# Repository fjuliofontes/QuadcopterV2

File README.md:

# Quadcopter V2
## This repository contains a work in progress of the second version of my previous quadcopter project.
## This version will support all modes of control.

### Main controller board hardware:
  - 1 x [ESP-01 for Wifi support](https://www.aliexpress.com/item/33018645469.html)
  - 1 x [HC-SR04 for landing support](https://www.aliexpress.com/item/32981718332.html)
  - 1 x [HC-05 for Bluetooth support](https://www.aliexpress.com/item/32953559442.html)
  - 2 x [HC-12 for RF communication](https://www.aliexpress.com/item/32971735328.html)
  - 1 x [MPU-6050 gyro/accelerometer for auto-level feature](https://www.aliexpress.com/item/32346328217.html)
  - 1 x [MS5611 Barometer for altitude hold function](https://www.aliexpress.com/item/4000436844936.html)
  - 1 x [SIM800L V2 for GSM & TCP communication](https://www.aliexpress.com/item/32467842817.html)
  - 1 x [U-blox M8 Engine GPS for heading lock and GPS hold function](https://www.dx.com/p/72-channel-u-blox-m8-engine-gps-module-for-fpv-multicopter-black-2069966.html)
  - 1 x [Texas-EK-TM4C123GXL for running the main software](http://www.ti.com/tool/EK-TM4C123GXL)
  
 ### Quadcopter housing hardware:
  - 1 x [450 size frame with integrated power distribution board](https://www.aliexpress.com/item/4000129400366.html)
  - 4 x [1000kV motor / 10x4.5 props / ESC combo](https://www.aliexpress.com/item/2035093137.html)
  - 1 x [3S / 2200mAh / 30C lipo](https://www.dx.com/p/11-1v-2200mah-30c-li-polymer-battery-pack-for-450-helicopter-dji-phantom-1-450-quadcopter-2048977.html#.Xlpl7C2tEWo)
  - 1 x [Battery XT60 connector](https://www.aliexpress.com/item/33061763696.html)
  - 1 x [2S/3S lipo battery charger](https://www.aliexpress.com/item/4000106254839.html)
  
  #### [Version 1.0](https://github.com/fjuliofontes/Quadcopter)
  
  ##### TODO:
  - [x] Order the necessary hardware.
  - [x] Test and develop code for ordered hardware.
  - [x] Design a schematic and a board for the hardware.
  - [x] Develop a controller algorithm for the quadcopter.
  - [x] Update the android remote controller application.
  - [x] Testing all together. 
  
  ##### Media:

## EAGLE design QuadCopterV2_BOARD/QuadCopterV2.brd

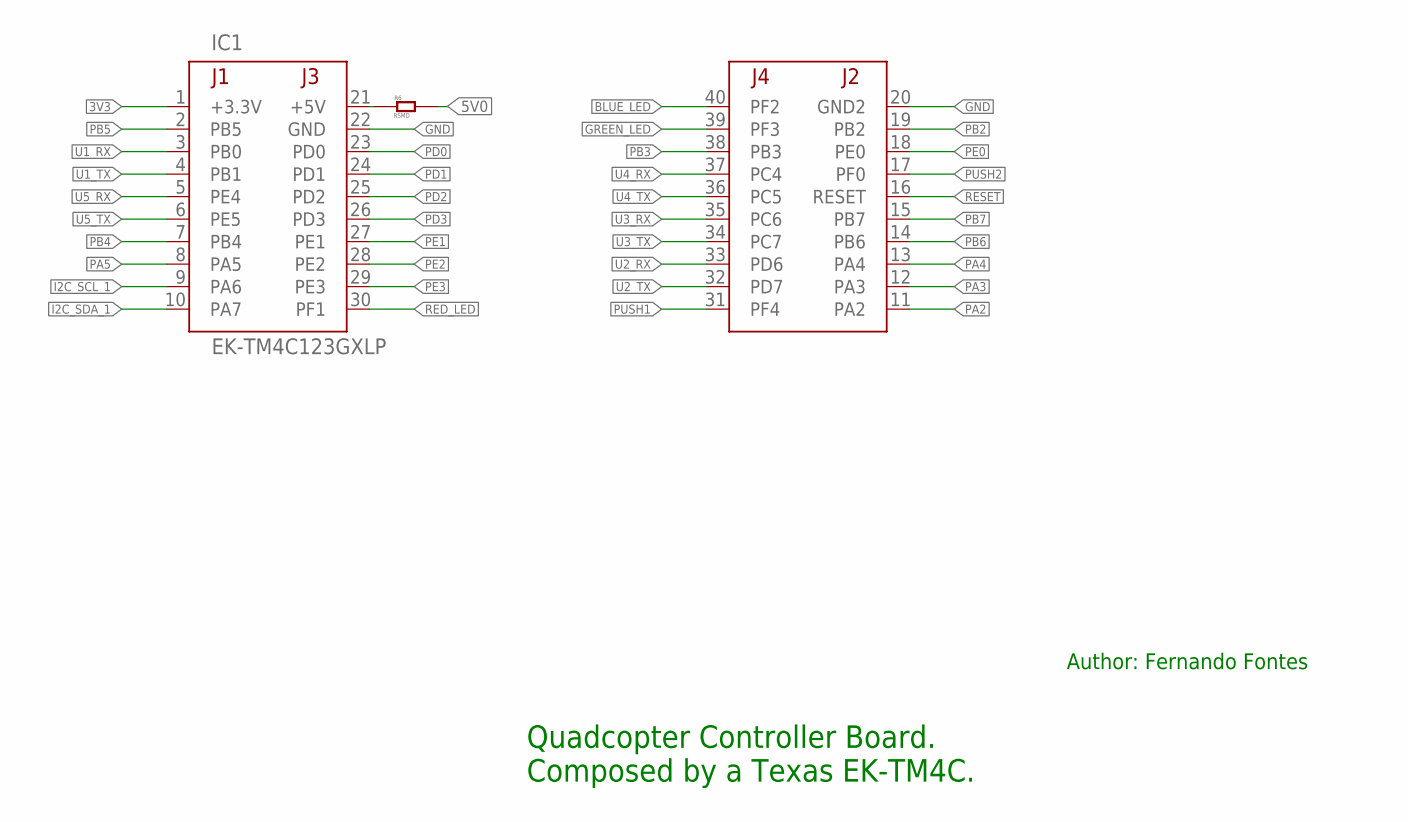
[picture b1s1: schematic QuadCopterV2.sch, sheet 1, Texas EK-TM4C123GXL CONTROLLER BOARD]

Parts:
IC1: EK-TM4C123GXLP; TM4C123LAUNCHPAD
R6: RSMD

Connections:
3V3: IC1.1 (+3.3V)
5V0: R6.2; also elsewhere on the board
BLUE_LED: IC1.40 (PF2)
GND: IC1.20 (GND2), IC1.22 (GND); also elsewhere on the board
GREEN_LED: IC1.39 (PF3)
I2C_SCL_1: IC1.9 (PA6); also elsewhere on the board
I2C_SDA_1: IC1.10 (PA7); also elsewhere on the board
unnamed: IC1.21 (+5V), R6.1
PA2: IC1.11 (PA2); also elsewhere on the board
PA3: IC1.12 (PA3)
PA4: IC1.13 (PA4)
PA5: IC1.8 (PA5); also elsewhere on the board
PB2: IC1.19 (PB2); also elsewhere on the board
PB3: IC1.38 (PB3)
PB4: IC1.7 (PB4); also elsewhere on the board
PB5: IC1.2 (PB5); also elsewhere on the board
PB6: IC1.14 (PB6); also elsewhere on the board
PB7: IC1.15 (PB7); also elsewhere on the board
PD0: IC1.23 (PD0); also elsewhere on the board
PD1: IC1.24 (PD1); also elsewhere on the board
PD2: IC1.25 (PD2)
PD3: IC1.26 (PD3); also elsewhere on the board
PE0: IC1.18 (PE0)
PE1: IC1.27 (PE1); also elsewhere on the board
PE2: IC1.28 (PE2); also elsewhere on the board
PE3: IC1.29 (PE3)
PUSH1: IC1.31 (PF4)
PUSH2: IC1.17 (PF0)
RED_LED: IC1.30 (PF1)
RESET: IC1.16 (RESET)
U1_RX: IC1.3 (PB0); also elsewhere on the board
U1_TX: IC1.4 (PB1); also elsewhere on the board
U2_RX: IC1.33 (PD6); also elsewhere on the board
U2_TX: IC1.32 (PD7); also elsewhere on the board
U3_RX: IC1.35 (PC6); also elsewhere on the board
U3_TX: IC1.34 (PC7); also elsewhere on the board
U4_RX: IC1.37 (PC4); also elsewhere on the board
U4_TX: IC1.36 (PC5); also elsewhere on the board
U5_RX: IC1.5 (PE4); also elsewhere on the board
U5_TX: IC1.6 (PE5); also elsewhere on the board

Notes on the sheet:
Quadcopter Controller Board. Composed by a Texas EK-TM4C.
Author: Fernando Fontes

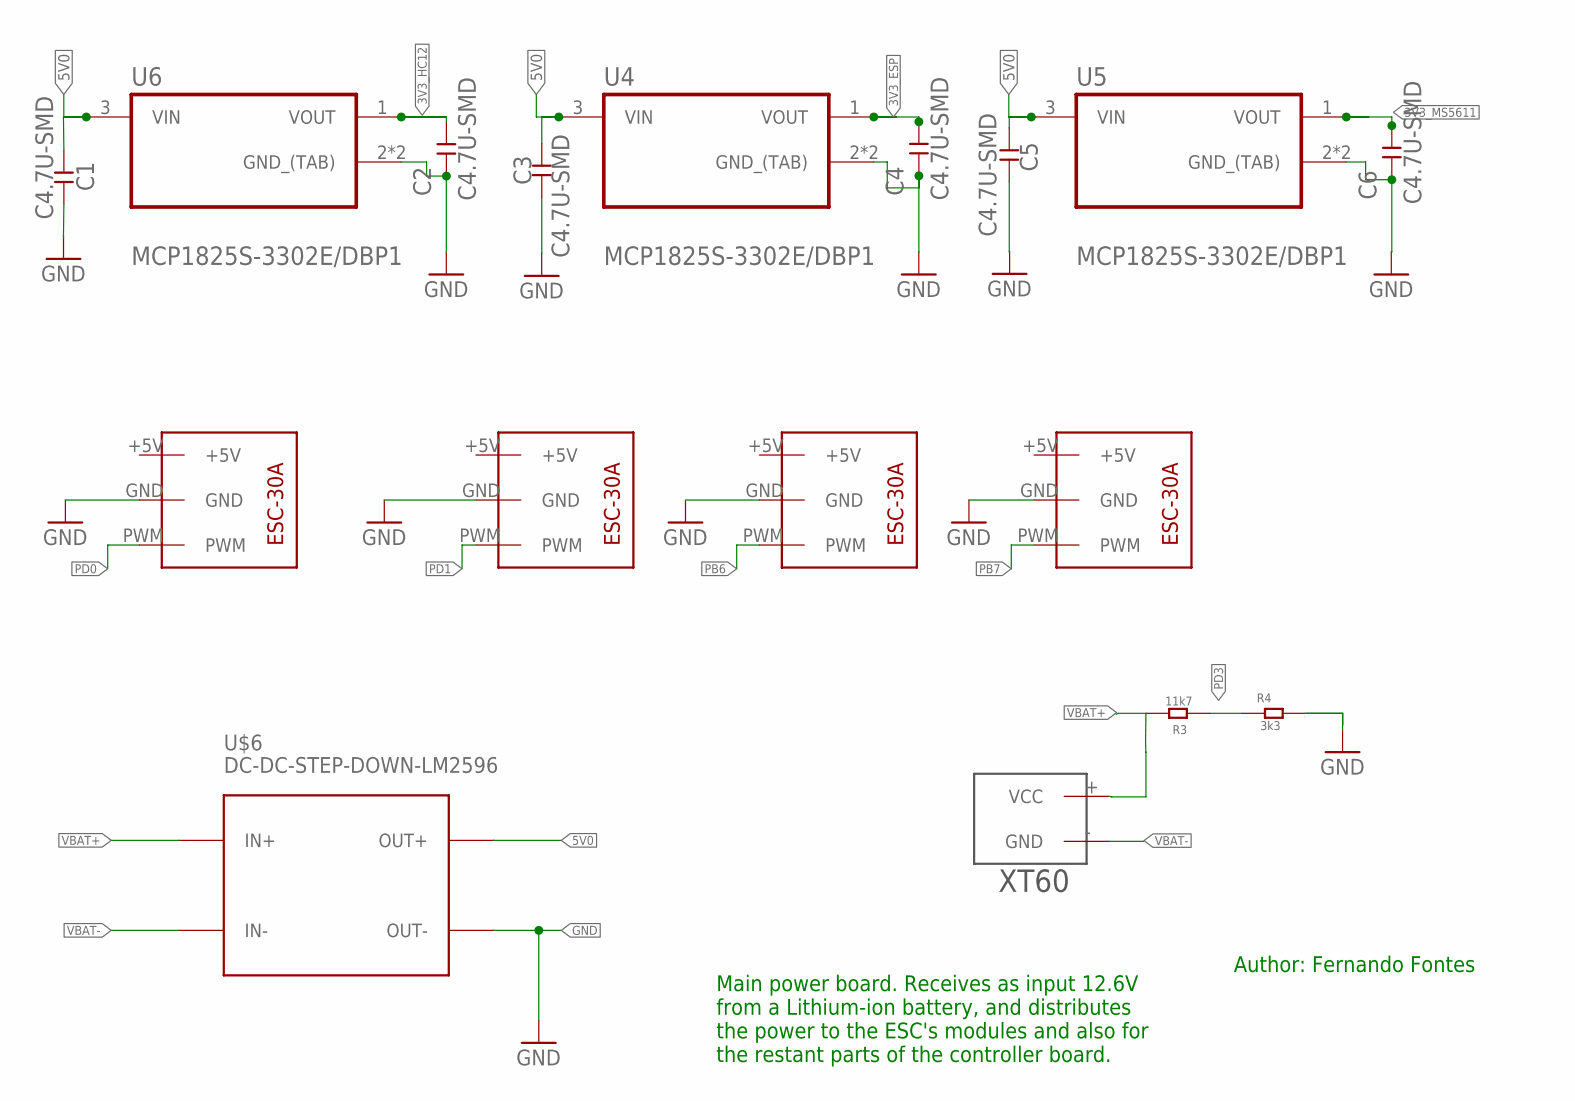
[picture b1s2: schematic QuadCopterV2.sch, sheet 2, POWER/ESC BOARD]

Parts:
C1, C2, C3, C4, C5, C6: C4.7U-SMD
R3: 11k7; RSMD
R4: 3k3; RSMD
U4, U5, U6: MCP1825S-3302E/DBP1; SOT230P700X180-4N#P1
U7, U8, U9, U10: ESC-30AMS5611; ESC-30A
U$6: DC-DC-STEP-DOWN-LM2596
U$7: XT60

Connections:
3V3_ESP: C4.2, U4.1 (VOUT); also elsewhere on the board
3V3_HC12: C2.2, U6.1 (VOUT); also elsewhere on the board
3V3_MS5611: C6.2, U5.1 (VOUT); also elsewhere on the board
5V0: C1.1, C3.2, C5.1, U4.3 (VIN), U5.3 (VIN), U6.3 (VIN), U$6.OUT+; also elsewhere on the board
GND: C1.2, C2.1, C3.1, C4.1, C5.2, C6.1, R4.2, U4.2 (GND_(TAB)), U4.4 (GND_(TAB)), U5.2 (GND_(TAB)), U5.4 (GND_(TAB)), U6.2 (GND_(TAB)), U6.4 (GND_(TAB)), U7.GND, U8.GND, U9.GND, U10.GND, U$6.OUT-; also elsewhere on the board
PB6: U9.PWM; also elsewhere on the board
PB7: U10.PWM; also elsewhere on the board
PD0: U7.PWM; also elsewhere on the board
PD1: U8.PWM; also elsewhere on the board
PD3: R3.1, R4.1; also elsewhere on the board
VBAT+: R3.2, U$6.IN+, U$7.+ (VCC)
VBAT-: U$6.IN-, U$7.- (GND)

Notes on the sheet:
Main power board. Receives as input 12.6V from a Lithium-ion battery, and distributes the power to the ESC's modules and also for the restant parts of the controller board.
Author: Fernando Fontes

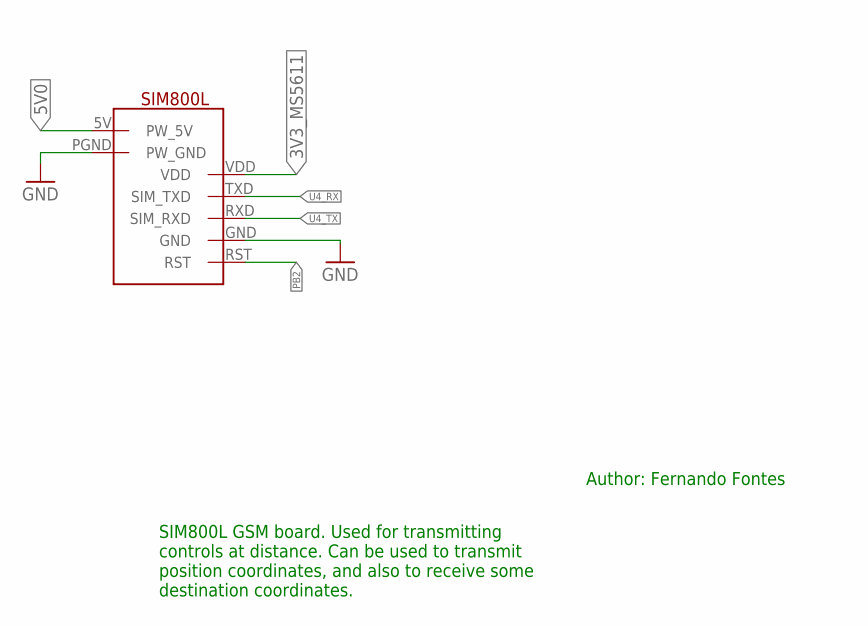
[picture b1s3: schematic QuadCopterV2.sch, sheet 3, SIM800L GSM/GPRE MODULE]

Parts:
U$1: SIM800L; SIP

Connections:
3V3_MS5611: U$1.VDD; also elsewhere on the board
5V0: U$1.5V (PW_5V); also elsewhere on the board
GND: U$1.GND, U$1.PGND (PW_GND); also elsewhere on the board
PB2: U$1.RST; also elsewhere on the board
U4_RX: U$1.TXD (SIM_TXD); also elsewhere on the board
U4_TX: U$1.RXD (SIM_RXD); also elsewhere on the board

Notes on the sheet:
Author: Fernando Fontes
SIM800L GSM board. Used for transmitting controls at distance. Can be used to transmit position coordinates, and also to receive some destination coordinates.

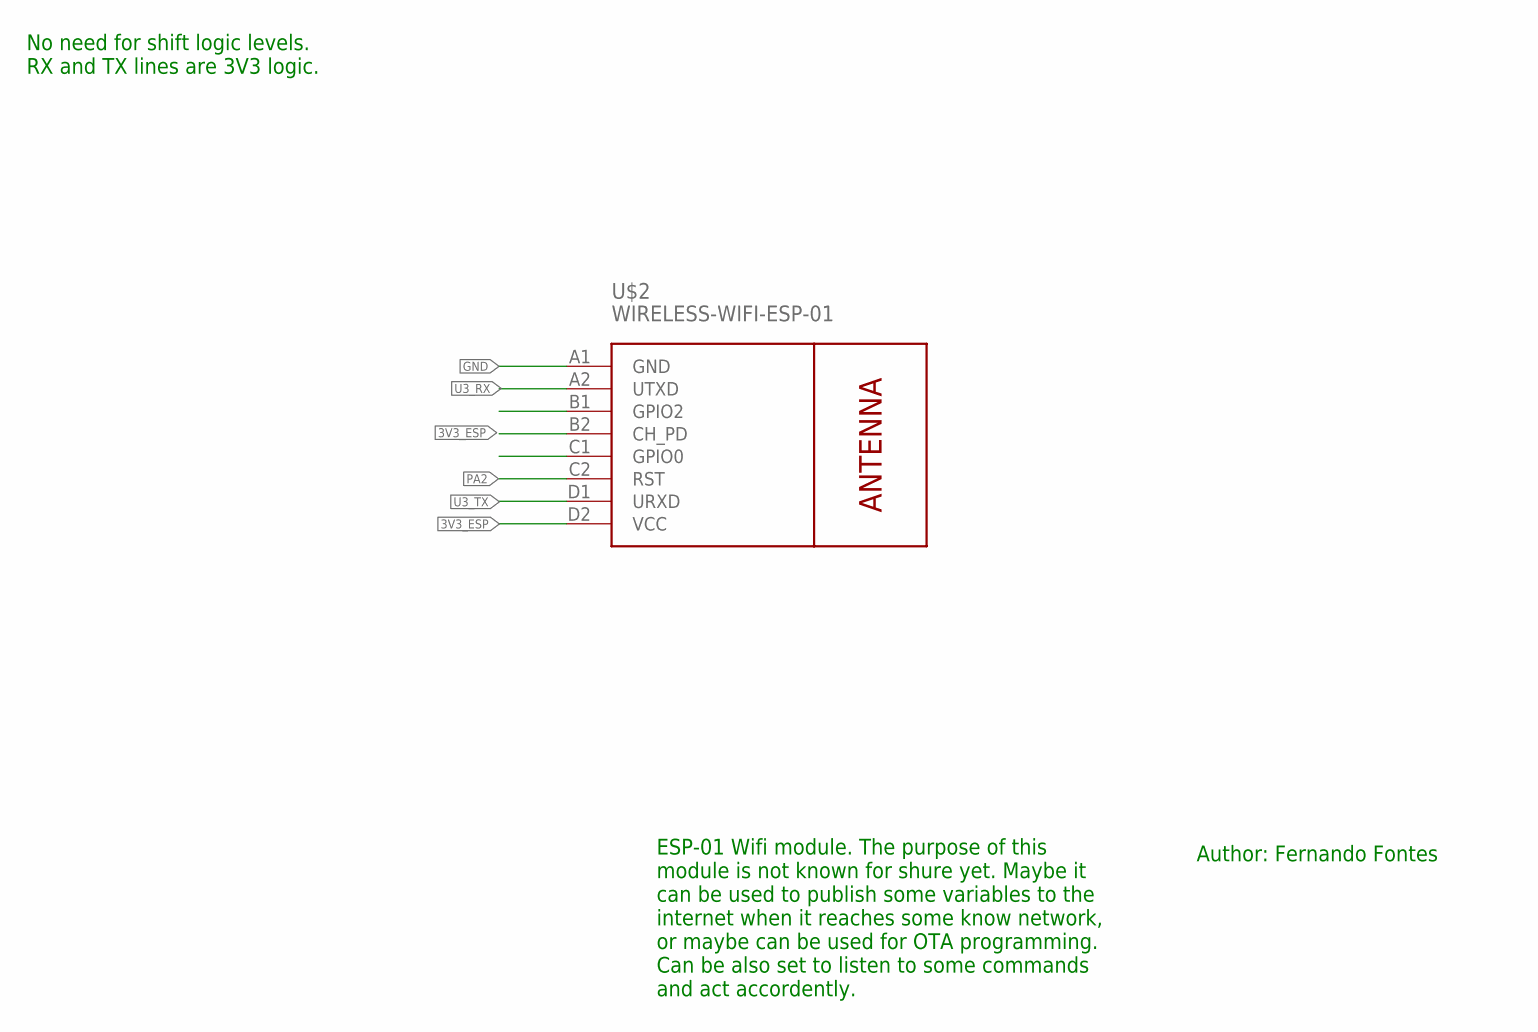
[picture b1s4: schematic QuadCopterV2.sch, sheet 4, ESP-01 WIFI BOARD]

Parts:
U$2: WIRELESS-WIFI-ESP-01

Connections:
3V3_ESP: U$2.B2 (CH_PD), U$2.D2 (VCC); also elsewhere on the board
GND: U$2.A1 (GND); also elsewhere on the board
PA2: U$2.C2 (RST); also elsewhere on the board
U3_RX: U$2.A2 (UTXD); also elsewhere on the board
U3_TX: U$2.D1 (URXD); also elsewhere on the board

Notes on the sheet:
No need for shift logic levels. RX and TX lines are 3V3 logic.
Author: Fernando Fontes
ESP-01 Wifi module. The purpose of this module is not known for shure yet. Maybe it can be used to publish some variables to the internet when it reaches some know network, or maybe can be used for OTA programming. Can be also set to listen to some commands and act accordently.

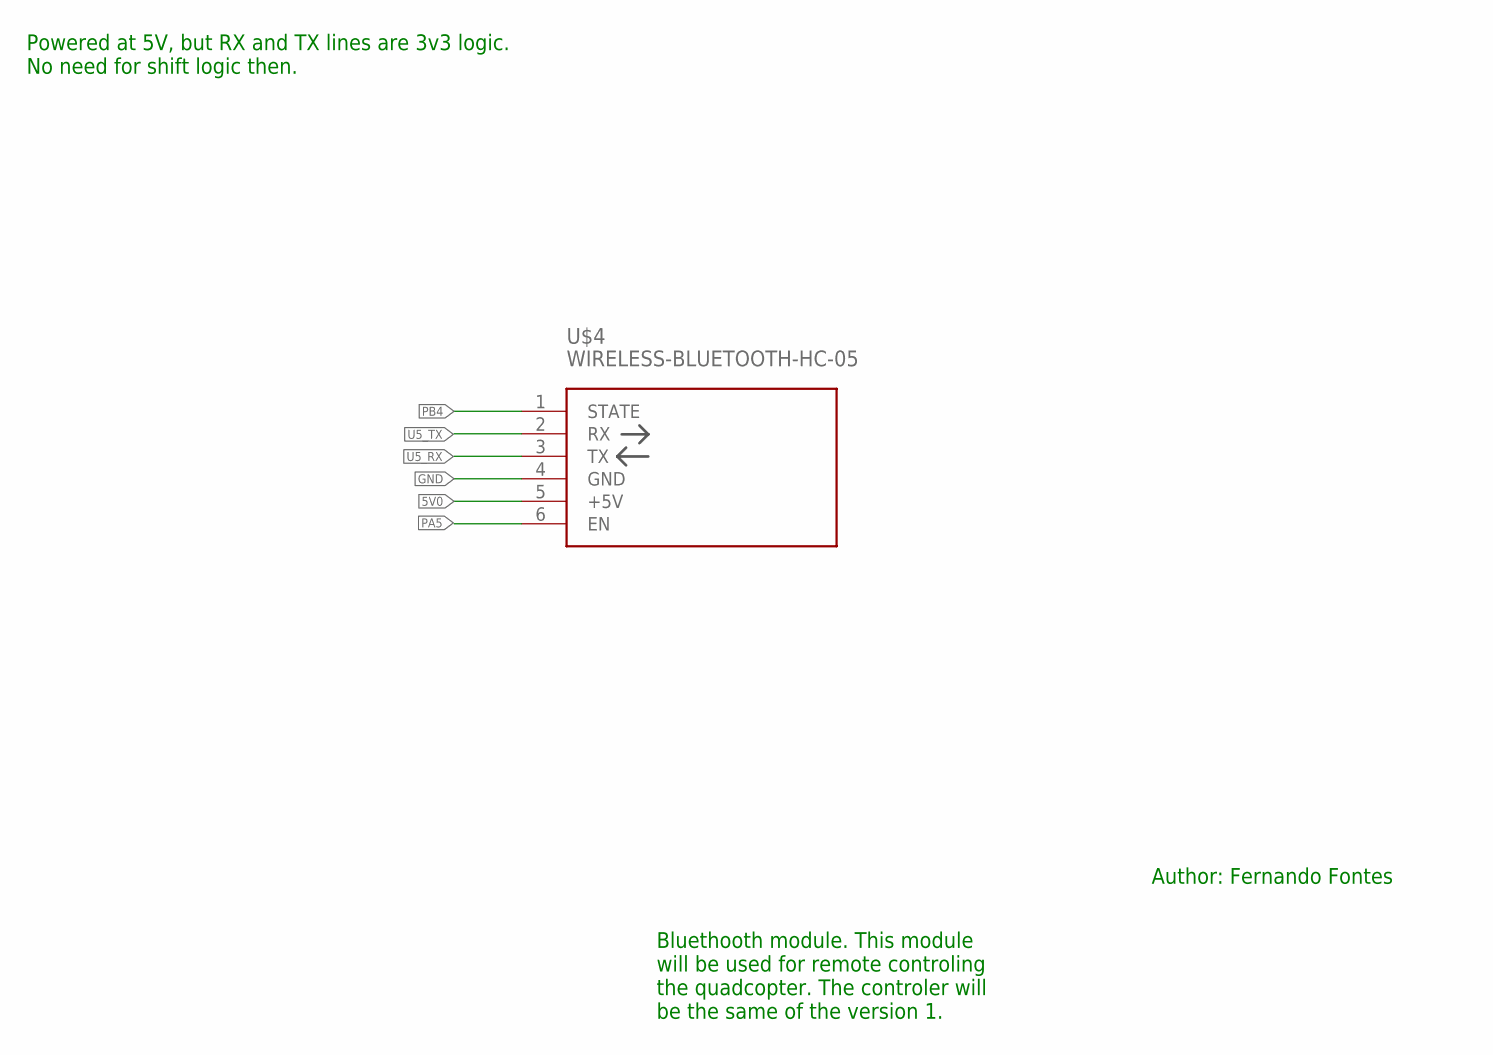
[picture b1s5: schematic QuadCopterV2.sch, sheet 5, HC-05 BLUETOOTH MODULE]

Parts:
U$4: WIRELESS-BLUETOOTH-HC-05

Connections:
5V0: U$4.5 (+5V); also elsewhere on the board
GND: U$4.4 (GND); also elsewhere on the board
PA5: U$4.6 (EN); also elsewhere on the board
PB4: U$4.1 (STATE); also elsewhere on the board
U5_RX: U$4.3 (TX); also elsewhere on the board
U5_TX: U$4.2 (RX); also elsewhere on the board

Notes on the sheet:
Powered at 5V, but RX and TX lines are 3v3 logic. No need for shift logic then.
Author: Fernando Fontes
Bluethooth module. This module will be used for remote controling the quadcopter. The controler will be the same of the version 1.

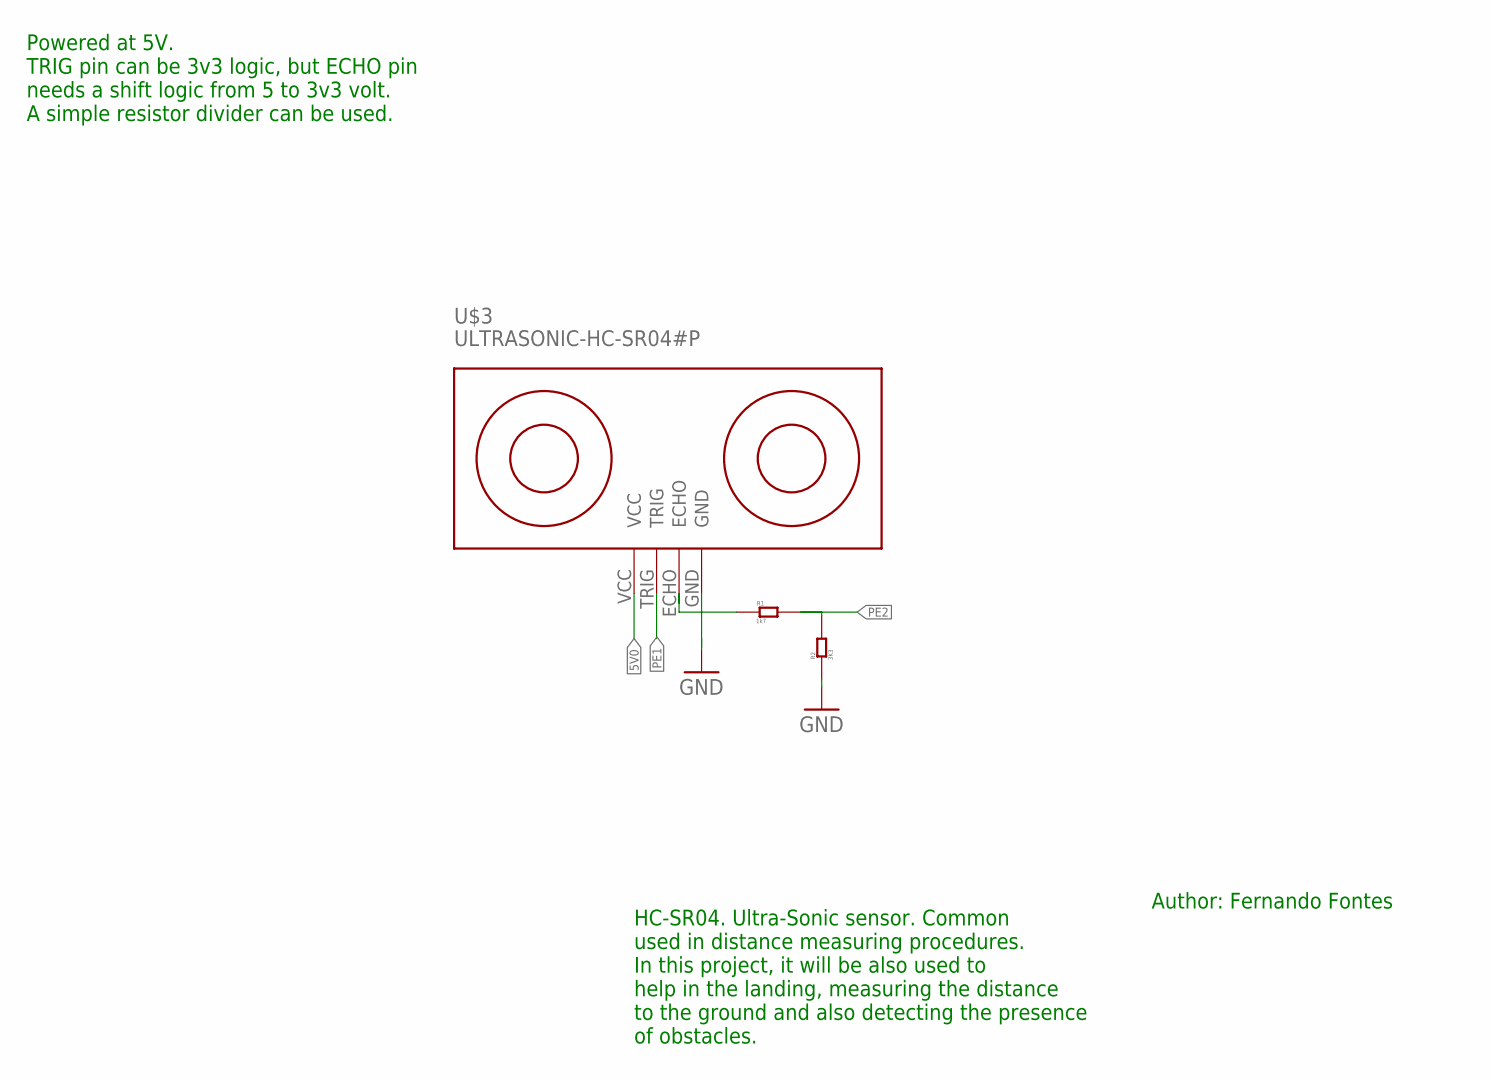
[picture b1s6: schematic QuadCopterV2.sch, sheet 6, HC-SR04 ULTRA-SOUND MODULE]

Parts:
R1: 1k7; RSMD
R2: 3K3; RSMD
U$3: ULTRASONIC-HC-SR04#P

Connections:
5V0: U$3.VCC; also elsewhere on the board
GND: R2.1, U$3.GND; also elsewhere on the board
unnamed: R1.1, U$3.ECHO
PE1: U$3.TRIG; also elsewhere on the board
PE2: R1.2, R2.2; also elsewhere on the board

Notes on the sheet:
Powered at 5V. TRIG pin can be 3v3 logic, but ECHO pin needs a shift logic from 5 to 3v3 volt. A simple resistor divider can be used.
Author: Fernando Fontes
HC-SR04. Ultra-Sonic sensor. Common used in distance measuring procedures. In this project, it will be also used to help in the landing, measuring the distance to the ground and also detecting the presence of obstacles.

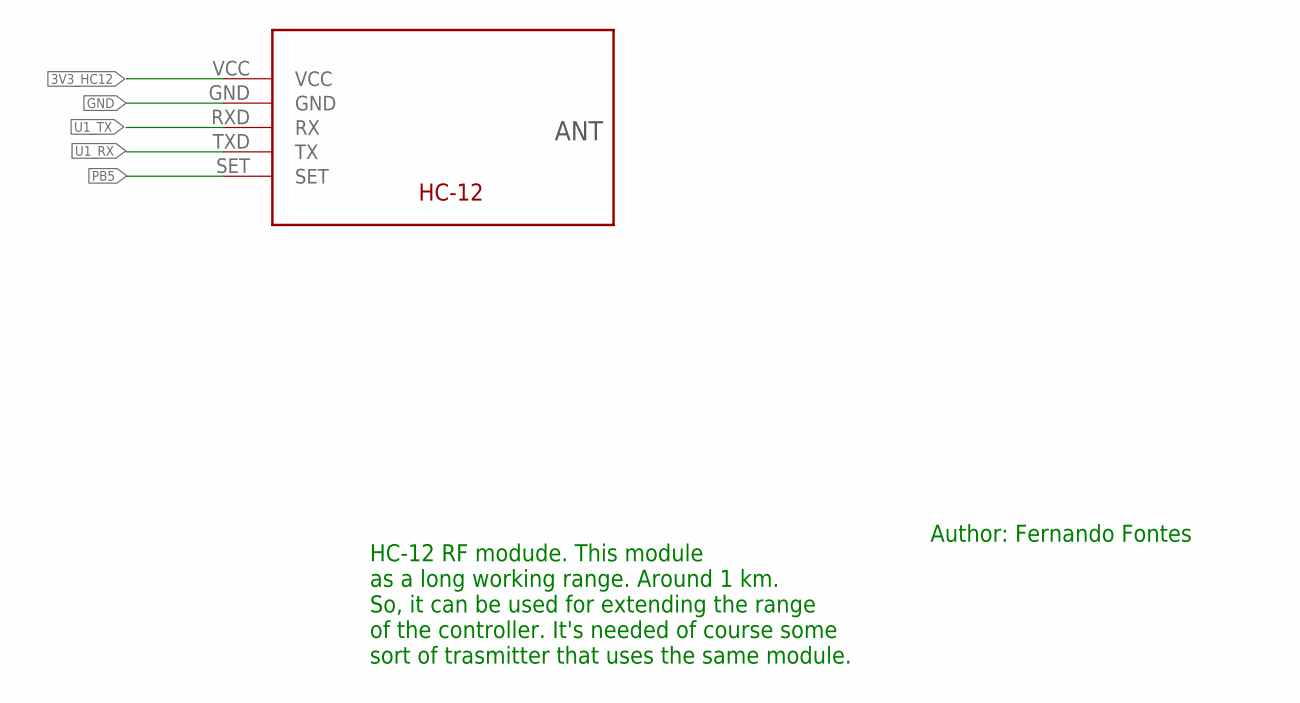
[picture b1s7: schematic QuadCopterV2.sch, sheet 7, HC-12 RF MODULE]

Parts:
U$5: HC-12_FOOTPRINT

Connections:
3V3_HC12: U$5.VCC; also elsewhere on the board
GND: U$5.GND; also elsewhere on the board
PB5: U$5.SET; also elsewhere on the board
U1_RX: U$5.TXD (TX); also elsewhere on the board
U1_TX: U$5.RXD (RX); also elsewhere on the board

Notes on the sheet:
Author: Fernando Fontes
HC-12 RF modude. This module as a long working range. Around 1 km. So, it can be used for extending the range of the controller. It's needed of course some sort of trasmitter that uses the same module.
ANT

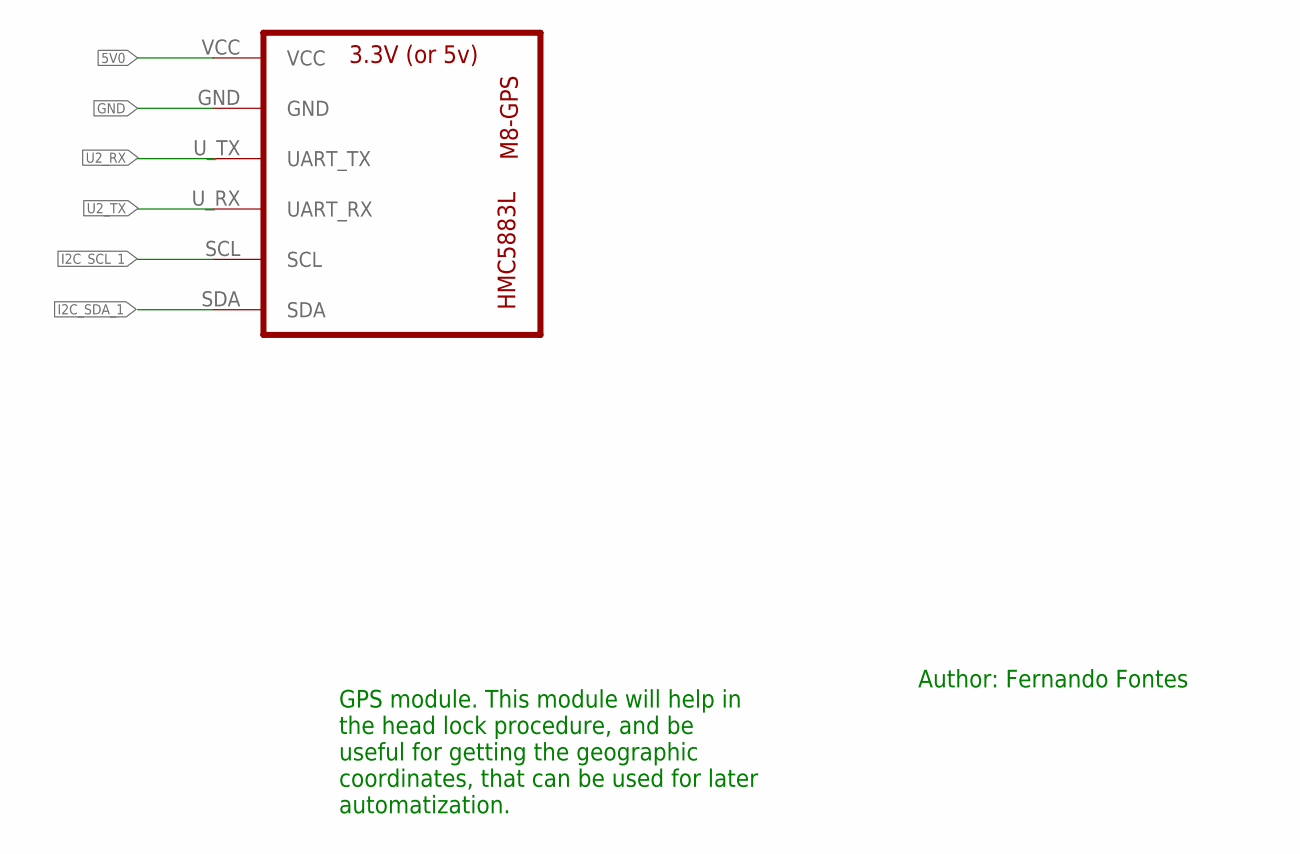
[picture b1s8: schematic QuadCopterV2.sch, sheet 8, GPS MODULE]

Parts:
U3: GY-63MS5611; U-BLOX

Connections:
5V0: U3.VCC; also elsewhere on the board
GND: U3.GND; also elsewhere on the board
I2C_SCL_1: U3.SCL; also elsewhere on the board
I2C_SDA_1: U3.SDA; also elsewhere on the board
U2_RX: U3.U_TX (UART_TX); also elsewhere on the board
U2_TX: U3.U_RX (UART_RX); also elsewhere on the board

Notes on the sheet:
Author: Fernando Fontes
GPS module. This module will help in the head lock procedure, and be useful for getting the geographic coordinates, that can be used for later automatization.

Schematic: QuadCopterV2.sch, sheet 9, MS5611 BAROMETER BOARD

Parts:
U1: GY-63MS5611; GY-63

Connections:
3V3_MS5611: U1.VCC; also elsewhere on the board
GND: U1.GND; also elsewhere on the board
I2C_SCL_1: U1.SCL; also elsewhere on the board
I2C_SDA_1: U1.SDA; also elsewhere on the board

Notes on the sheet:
Author: Fernando Fontes
Barometer module. This module will be the master piece for the altitude lock mode. Used for locking altitude and to other things.

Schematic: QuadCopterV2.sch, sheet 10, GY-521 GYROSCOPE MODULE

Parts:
U2: GY-521MPU6050; GY-521

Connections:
5V0: U2.VCC; also elsewhere on the board
GND: U2.GND; also elsewhere on the board
I2C_SCL_1: U2.SCL; also elsewhere on the board
I2C_SDA_1: U2.SDA; also elsewhere on the board

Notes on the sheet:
Author: Fernando Fontes
Gyroscope module. Used for the stabilization procedure. Has an internal accelerometer too.
Powered at 5v. However, SCL and SDA lines are 3v3 pulled up. So no need for shift logic converter.

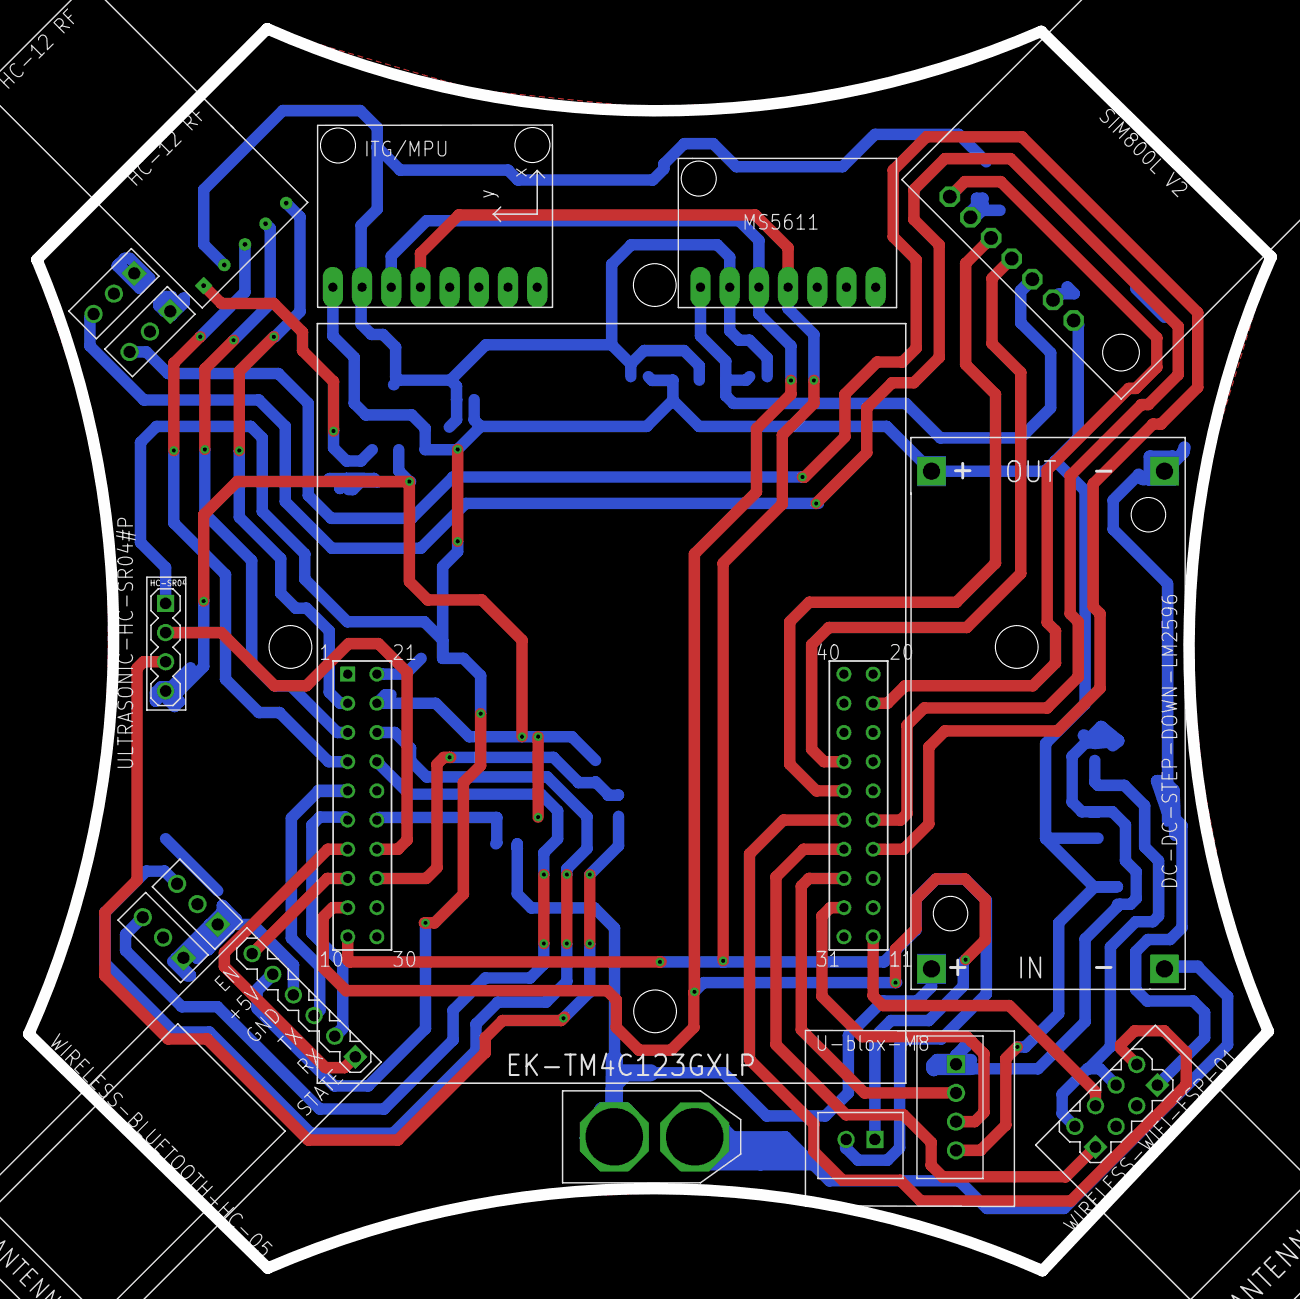
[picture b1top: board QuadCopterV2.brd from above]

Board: 2 copper layers, 108.1 x 108.1 mm, 29 parts (0 on the bottom side), 33 nets.

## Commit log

2020-02-27 README.md
2020-02-27 first push, with hardware datasheets
2020-02-29 minor changes and components names
2020-03-08 Eagle board design in process
2020-03-11 HC-05 library created
2020-03-12 HC-SR04 code added
2020-03-12 added MPU-6050 code
2020-03-17 added modifications to eagle board, and to the mpu-6050 code
2020-03-18 mpu-6050 finished, added more board eagle files, added altimeter code
2020-03-19 Added ESC modules
2020-03-20 news modifications on designed board
2020-03-21 final version of quadcopter board
2020-03-21 updted todo list
2020-03-23 added board rendered version
2020-03-25 added quadcopter image
2020-03-25 img updated
2020-05-07 added new code, still waiting for the components
2020-06-18 board sended to production
2020-06-18 added board render
2020-07-13 gps data acquiring process
2020-07-22 pcb arrived, some modules already soldered and tested
2020-07-22 added new images
2020-07-22 images updated
2020-07-25 added ESP-01 AT commands support
2020-07-26 added eeprom saving calibration support
2020-08-07 added code for hc-12
2020-08-13 hc-sr04 code modified, sim800l added, hc-12 added
2020-08-16 heading bugs fixed
2020-08-22 added ms5611 barometer module
2020-10-18 Updates in a lot of functions
2021-03-06 Added PID controllers. Tested and working! KPI needs to be adjusted.
2021-03-06 debug updated
2021-03-07 Added Python-GUI for helping the PID adjusting process. Fixed HC-05 issues
2021-03-14 updates to pid controller
2021-04-09 improvements to UI
2021-05-16 fixed inaccurate readings from the barometer sensor. Removed altitude PID, since we can't assure an accurate altitude reading and added hold altitude instead.
2021-08-28 added tool for setting the PID params remotly
2021-08-29 final touch to the pid setter script

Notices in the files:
parts and their libraries:
diy-modules: Released under the Creative Commons Attribution 4.0 International License: http://creativecommons.org/licenses/by/4.0
